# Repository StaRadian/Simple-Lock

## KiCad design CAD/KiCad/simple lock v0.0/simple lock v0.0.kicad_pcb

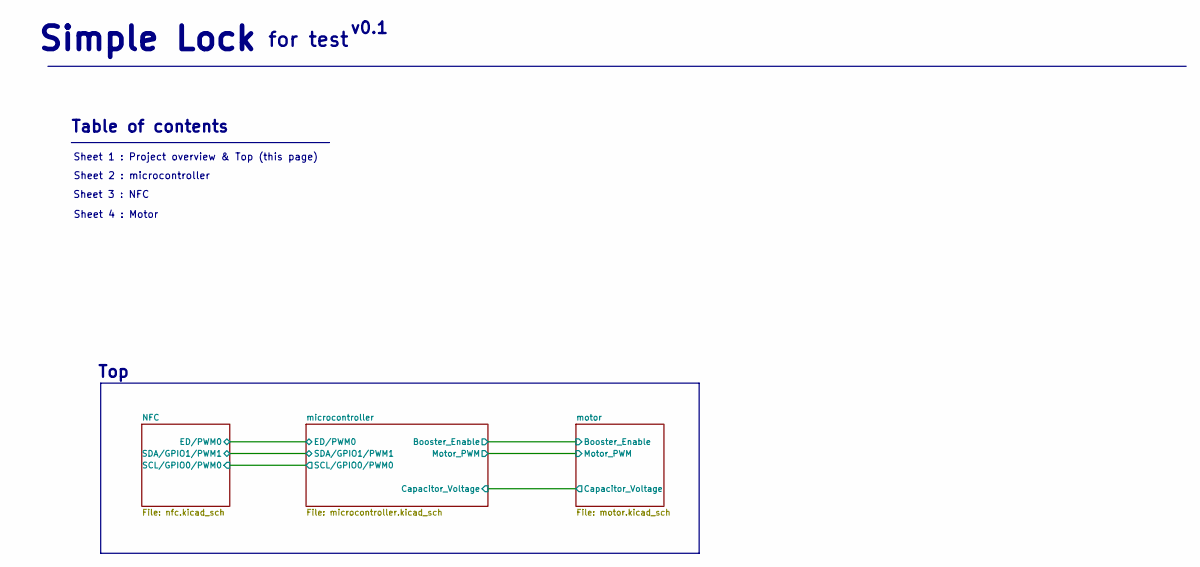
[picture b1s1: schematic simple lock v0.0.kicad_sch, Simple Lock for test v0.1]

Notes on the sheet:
v0.1
Top
Sheet 4 : Motor
for test
Sheet 2 : microcontroller
Table of contents
Sheet 3 : NFC
Simple Lock
Sheet 1 : Project overview & Top (this page)

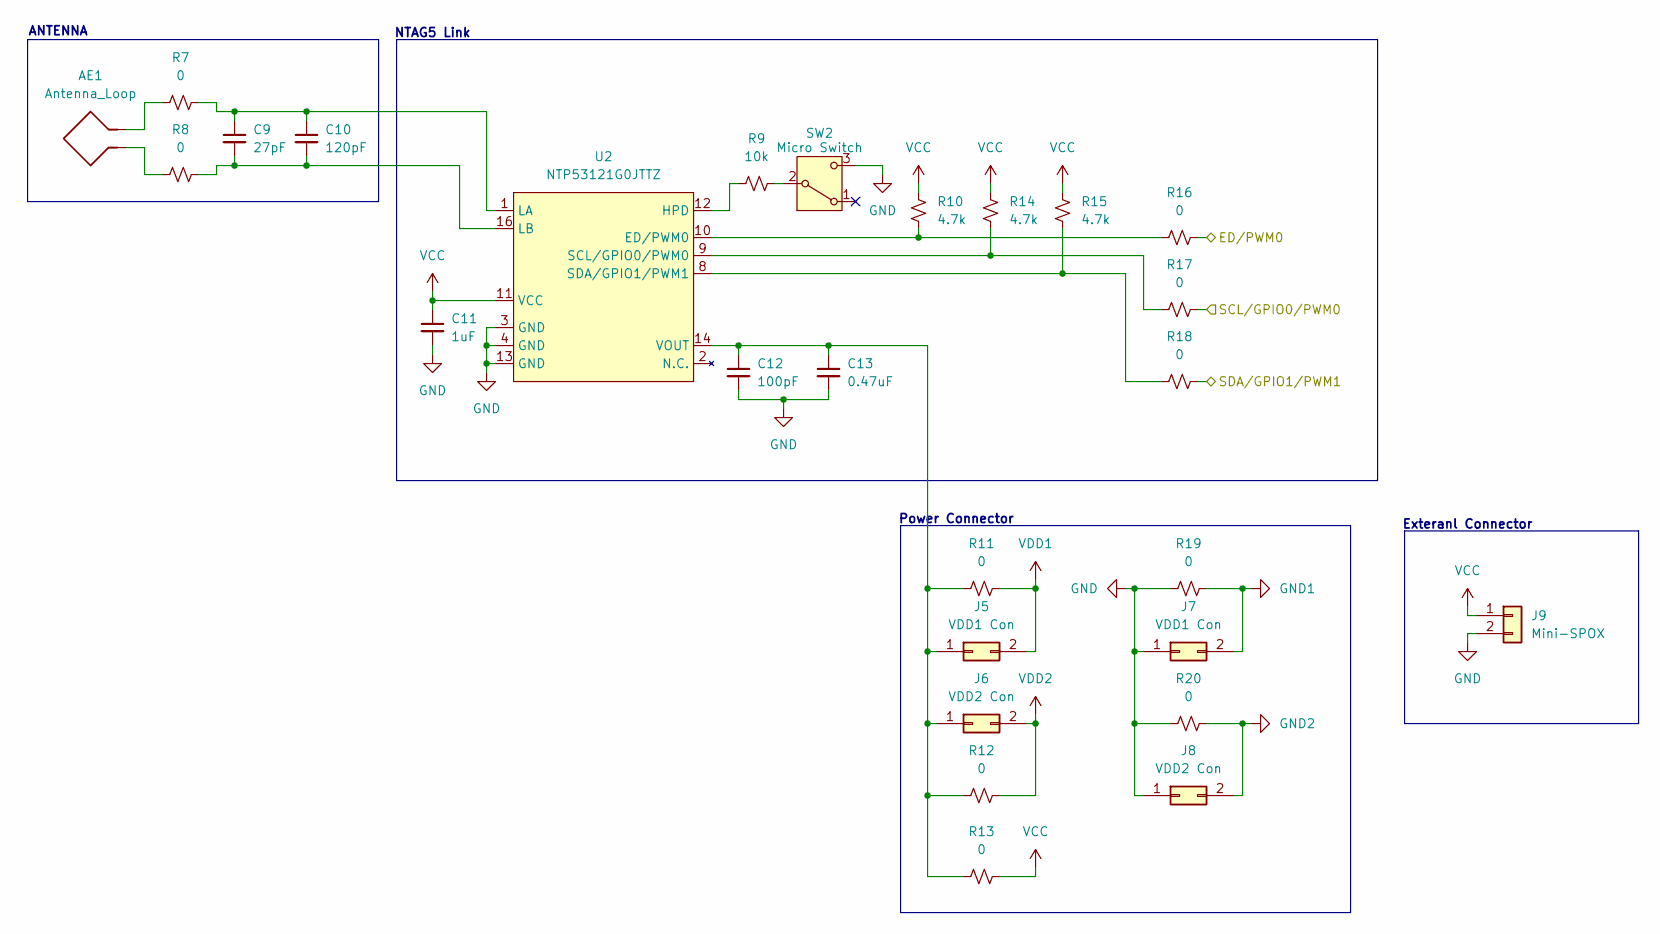
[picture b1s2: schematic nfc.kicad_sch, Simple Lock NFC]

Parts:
AE1: Antenna_Loop; Antenna_54x27mm
C9: 27pF; 0603_1608_C
C10: 120pF; 0603_1608_C
C11: 1uF; 0603_1608_C
C12: 100pF; 0603_1608_C
C13: 0.47uF; 0603_1608_C
J5, J7: VDD1 Con; PinHeader_1x02_P2.54mm
J6, J8: VDD2 Con; PinHeader_1x02_P2.54mm
J9: Mini-SPOX; 5267-02A
R7, R8, R11, R12, R13, R16, R17, R18, R19, R20: 0; 0603_1608_R
R9: 10k; 0603_1608_R
R10, R14, R15: 4.7k; 0603_1608_R
SW2: Micro Switch; Reset Switch
U2: NTP53121G0JTTZ; SOT403-1

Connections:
/NFC/ED/PWM0: R16.2; also elsewhere on the board
/NFC/SCL/GPIO0/PWM0: R17.2; also elsewhere on the board
/NFC/SDA/GPIO1/PWM1: R18.2; also elsewhere on the board
GND: C11.2, C12.2, C13.2, J7.1, J8.1, J9.2, R19.1, R20.1, SW2.3 (C), U2.3 (GND), U2.4 (GND), U2.13 (GND)
GND1: J7.2, R19.2; also elsewhere on the board
GND2: J8.2, R20.2; also elsewhere on the board
unnamed: AE1.1, R8.2
unnamed: AE1.2, R7.2
unnamed: C12.1, C13.1, J5.1, J6.1, R11.1, R12.1, R13.1, U2.14 (VOUT)
unnamed: R9.1, SW2.2 (B)
unnamed: R10.2, R16.1, U2.10 (ED/PWM0)
unnamed: R9.2, U2.12 (HPD)
unnamed: C9.1, C10.1, R7.1, U2.1 (LA)
unnamed: C9.2, C10.2, R8.1, U2.16 (LB)
unnamed: R14.2, R17.1, U2.9 (SCL/GPIO0/PWM0)
unnamed: R15.2, R18.1, U2.8 (SDA/GPIO1/PWM1)
VCC: C11.1, J9.1, R10.1, R13.2, R14.1, R15.1, U2.11 (VCC)
VDD1: J5.2, R11.2; also elsewhere on the board
VDD2: J6.2, R12.2; also elsewhere on the board

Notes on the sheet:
Exteranl Connector
ANTENNA
Power Connector
NTAG5 Link

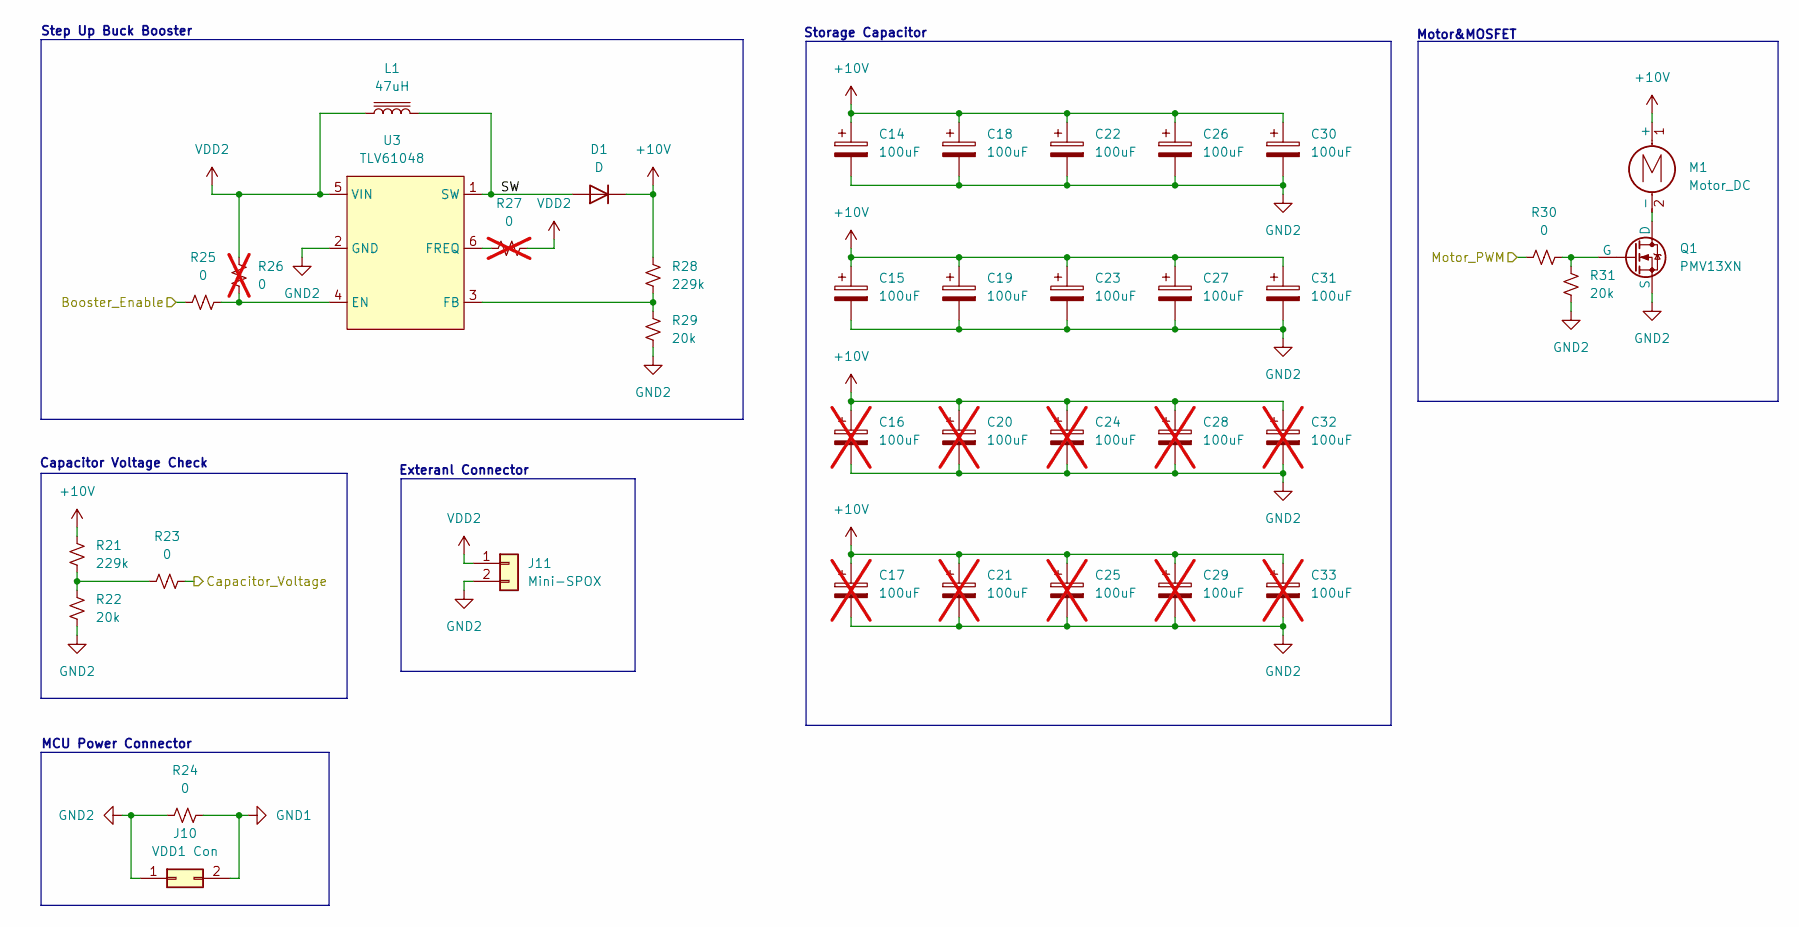
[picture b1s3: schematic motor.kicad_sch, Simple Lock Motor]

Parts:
C14, C15, C18, C19, C22, C23, C26, C27, C30, C31: 100uF; 1206_3216_C_Polarized_HandSolder
C16, C17, C20, C21, C24, C25, C28, C29, C32, C33: 100uF; 1206_3216_C_Polarized_HandSolder; not fitted
D1: D; SDMG0340L
J10: VDD1 Con; PinHeader_1x02_P2.54mm
J11: Mini-SPOX; 5267-02A
L1: 47uH; SER1390
M1: Motor_DC; Motor_Connector
Q1: PMV13XN; SOT-23
R21, R28: 229k; 0603_1608_R
R22, R29, R31: 20k; 0603_1608_R
R23, R24, R25, R30: 0; 0603_1608_R
R26, R27: 0; 0603_1608_R; not fitted
U3: TLV61048; SOT-23-6_HandSoldering

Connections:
+10V: C14.1, C15.1, C16.1, C17.1, C18.1, C19.1, C20.1, C21.1, C22.1, C23.1, C24.1, C25.1, C26.1, C27.1, C28.1, C29.1, C30.1, C31.1, C32.1, C33.1, D1.1 (K), M1.1 (+), R21.2, R28.2
/microcontroller/Booster_Enable: R25.2; also elsewhere on the board
/microcontroller/Capacitor_Voltage: R23.1; also elsewhere on the board
/microcontroller/Motor_PWM: R30.2; also elsewhere on the board
/motor/SW: D1.2 (A), L1.1, U3.1 (SW)
GND1: J10.2, R24.2; also elsewhere on the board
GND2: C14.2, C15.2, C16.2, C17.2, C18.2, C19.2, C20.2, C21.2, C22.2, C23.2, C24.2, C25.2, C26.2, C27.2, C28.2, C29.2, C30.2, C31.2, C32.2, C33.2, J10.1, J11.2, Q1.3 (S), R22.1, R24.1, R29.1, R31.1, U3.2 (GND); also elsewhere on the board
unnamed: M1.2 (-), Q1.1 (D)
unnamed: Q1.2 (G), R30.1, R31.2
unnamed: R21.1, R22.2, R23.2
unnamed: R25.1, R26.1, U3.4 (EN)
unnamed: R28.1, R29.2, U3.3 (FB)
unnamed: R27.2, U3.6 (FREQ)
VDD2: J11.1, L1.2, R26.2, R27.1, U3.5 (VIN); also elsewhere on the board

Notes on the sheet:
Storage Capacitor
MCU Power Connector
Motor&MOSFET
Exteranl Connector
Capacitor Voltage Check
Step Up Buck Booster

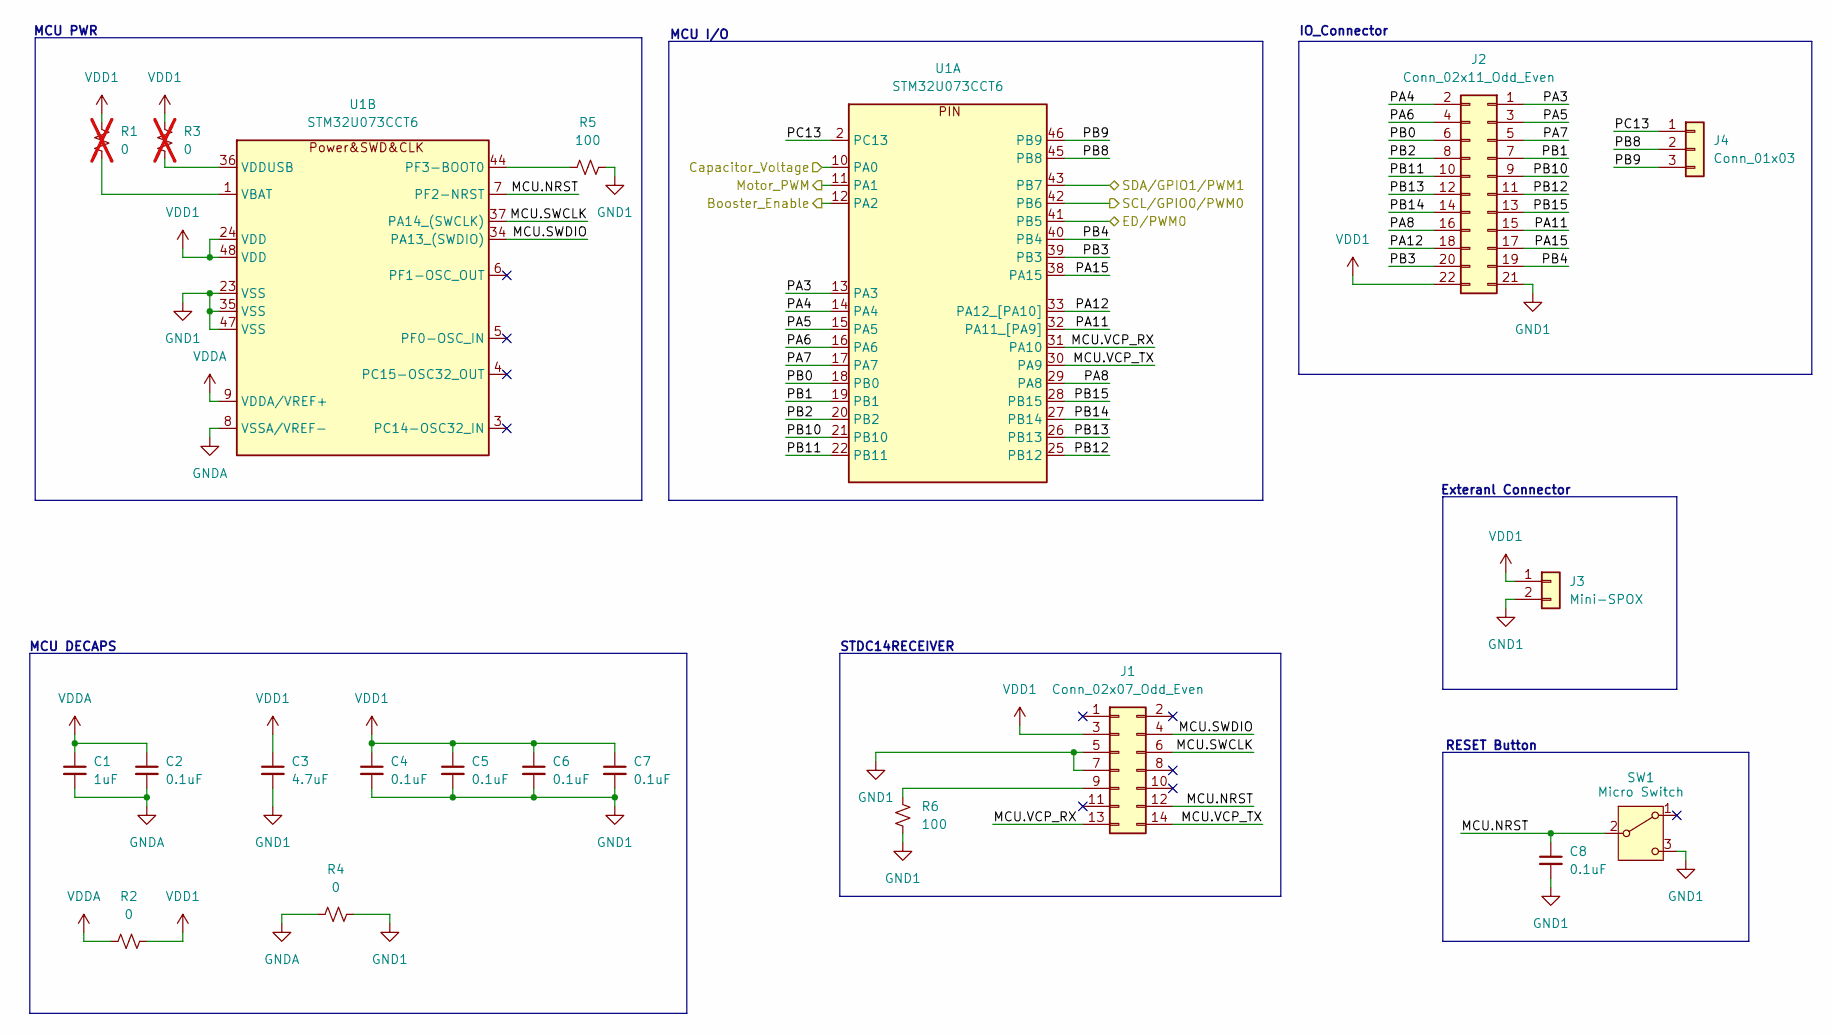
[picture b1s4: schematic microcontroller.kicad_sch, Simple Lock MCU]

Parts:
C1: 1uF; 0603_1608_C
C2, C4, C5, C6, C7, C8: 0.1uF; 0603_1608_C
C3: 4.7uF; 0603_1608_C
J1: Conn_02x07_Odd_Even; STDC14
J2: Conn_02x11_Odd_Even; PinHeader_02x11_P2.54mm
J3: Mini-SPOX; 5267-02A
J4: Conn_01x03; PinHeader_01x03_P2.54mm
R1, R3: 0; 0603_1608_R; not fitted
R2, R4: 0; 0603_1608_R
R5, R6: 100; 0603_1608_R
SW1: Micro Switch; Reset Switch
U1: STM32U073CCT6; LQFP-48_7x7mm_P0.5mm

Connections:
/NFC/ED/PWM0: U1.41 (PB5); also elsewhere on the board
/NFC/SCL/GPIO0/PWM0: U1.42 (PB6); also elsewhere on the board
/NFC/SDA/GPIO1/PWM1: U1.43 (PB7); also elsewhere on the board
/microcontroller/Booster_Enable: U1.12 (PA2); also elsewhere on the board
/microcontroller/Capacitor_Voltage: U1.10 (PA0); also elsewhere on the board
/microcontroller/MCU.NRST: C8.1, J1.12, SW1.2 (B), U1.7 (PF2-NRST)
/microcontroller/MCU.SWCLK: J1.6, U1.37 (PA14_(SWCLK))
/microcontroller/MCU.SWDIO: J1.4, U1.34 (PA13_(SWDIO))
/microcontroller/MCU.VCP_RX: J1.13, U1.31 (PA10)
/microcontroller/MCU.VCP_TX: J1.14, U1.30 (PA9)
/microcontroller/Motor_PWM: U1.11 (PA1); also elsewhere on the board
/microcontroller/PA3: J2.1, U1.13 (PA3)
/microcontroller/PA4: J2.2, U1.14 (PA4)
/microcontroller/PA5: J2.3, U1.15 (PA5)
/microcontroller/PA6: J2.4, U1.16 (PA6)
/microcontroller/PA7: J2.5, U1.17 (PA7)
/microcontroller/PA8: J2.16, U1.29 (PA8)
/microcontroller/PA11: J2.15, U1.32 (PA11_[PA9])
/microcontroller/PA12: J2.18, U1.33 (PA12_[PA10])
/microcontroller/PA15: J2.17, U1.38 (PA15)
/microcontroller/PB0: J2.6, U1.18 (PB0)
/microcontroller/PB1: J2.7, U1.19 (PB1)
/microcontroller/PB2: J2.8, U1.20 (PB2)
/microcontroller/PB3: J2.20, U1.39 (PB3)
/microcontroller/PB4: J2.19, U1.40 (PB4)
/microcontroller/PB8: J4.2, U1.45 (PB8)
/microcontroller/PB9: J4.3, U1.46 (PB9)
/microcontroller/PB10: J2.9, U1.21 (PB10)
/microcontroller/PB11: J2.10, U1.22 (PB11)
/microcontroller/PB12: J2.11, U1.25 (PB12)
/microcontroller/PB13: J2.12, U1.26 (PB13)
/microcontroller/PB14: J2.14, U1.27 (PB14)
/microcontroller/PB15: J2.13, U1.28 (PB15)
/microcontroller/PC13: J4.1, U1.2 (PC13)
GND1: C3.2, C4.2, C5.2, C6.2, C7.2, C8.2, J1.5, J1.7, J2.21, J3.2, R4.1, R5.2, R6.2, SW1.3 (C), U1.23 (VSS), U1.35 (VSS), U1.47 (VSS); also elsewhere on the board
GNDA: C1.2, C2.2, R4.2, U1.8 (VSSA/VREF-)
unnamed: J1.9, R6.1
unnamed: R5.1, U1.44 (PF3-BOOT0)
unnamed: R1.1, U1.1 (VBAT)
unnamed: R3.1, U1.36 (VDDUSB)
VDD1: C3.1, C4.1, C5.1, C6.1, C7.1, J1.3, J2.22, J3.1, R1.2, R2.1, R3.2, U1.24 (VDD), U1.48 (VDD); also elsewhere on the board
VDDA: C1.1, C2.1, R2.2, U1.9 (VDDA/VREF+)

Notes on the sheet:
MCU DECAPS
RESET Button
MCU PWR
MCU I/O
IO_Connector
STDC14RECEIVER
Exteranl Connector

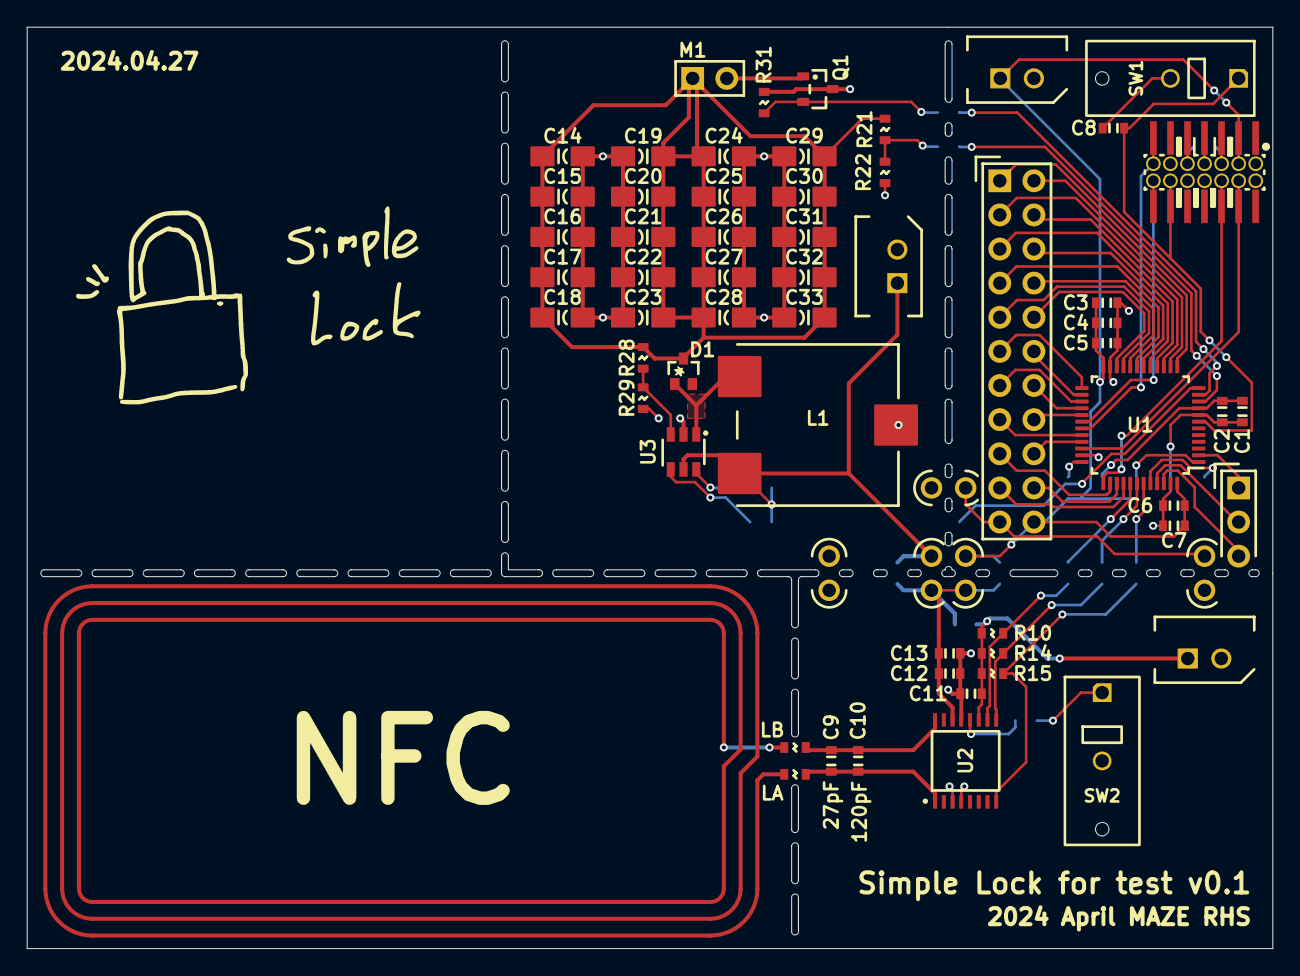
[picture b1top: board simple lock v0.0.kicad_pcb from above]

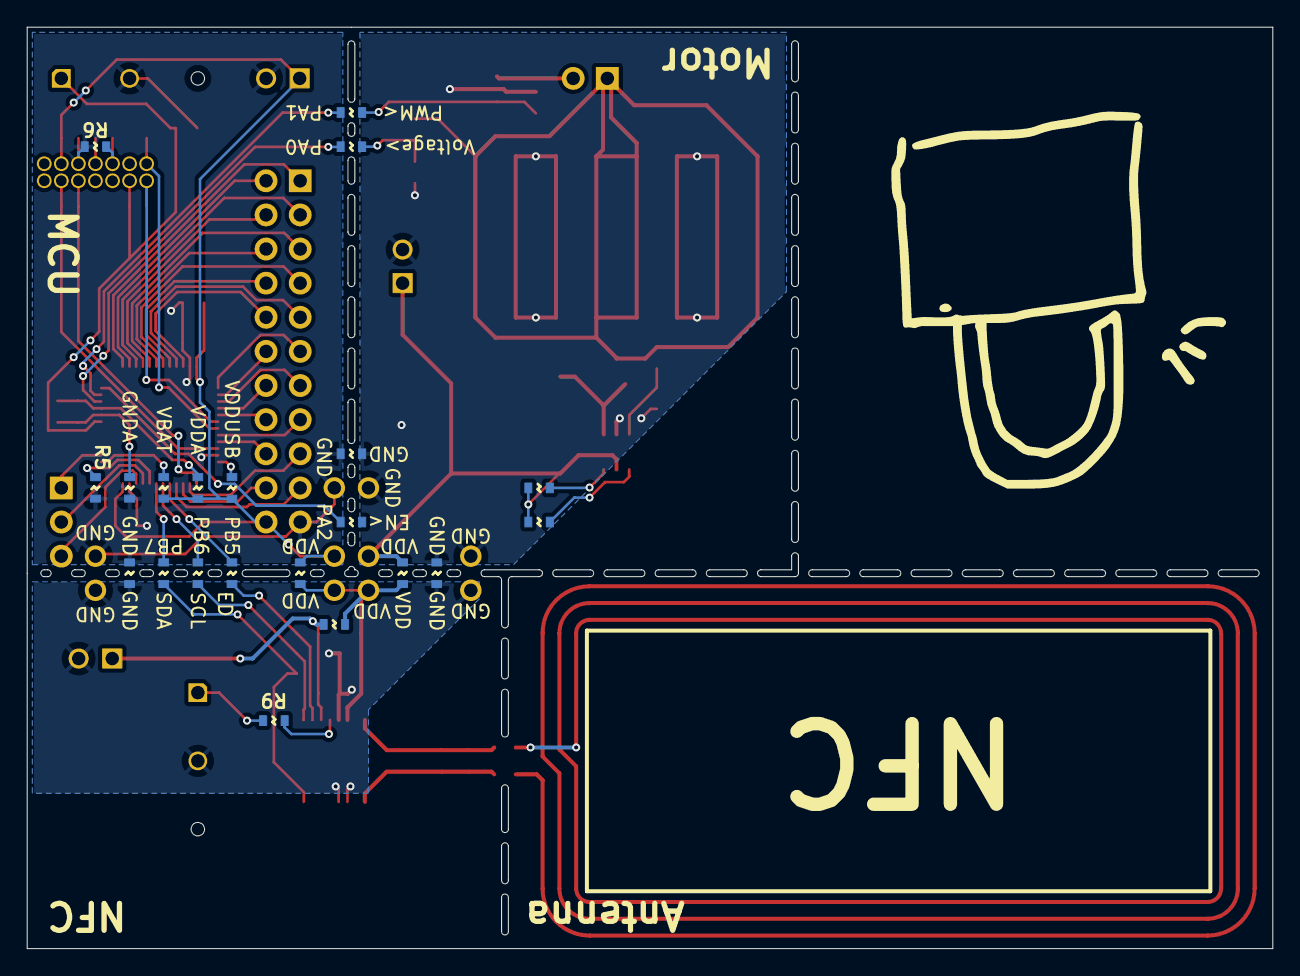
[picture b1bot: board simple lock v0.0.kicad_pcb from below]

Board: 2 copper layers, 92.7 x 68.6 mm, 85 parts (21 on the bottom side), 64 nets.
